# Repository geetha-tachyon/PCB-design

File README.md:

View this project on [CADLAB.io](https://cadlab.io/project/30245). 

# PCB-design
pcb design of stm32 and pressure sensor

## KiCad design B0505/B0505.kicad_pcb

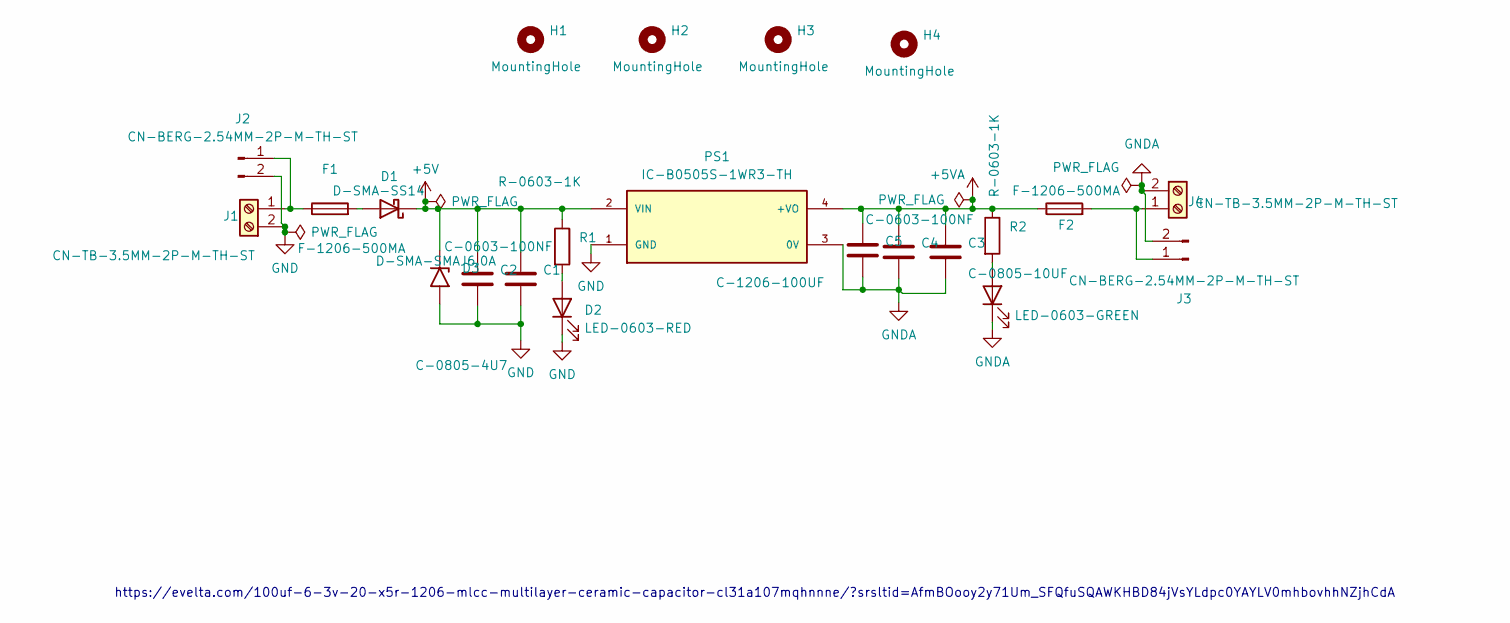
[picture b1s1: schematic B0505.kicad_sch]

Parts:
C1: C-0805-4U7; C_0805_2012Metric
C2, C4: C-0603-100NF; C_0603_1608Metric
C3: C-0805-10UF; C_0805_2012Metric
C5: C-1206-100UF; C_1206_3216Metric
D1: D-SMA-SS14; D_SMA
D2: LED-0603-RED; LED_0603_1608Metric
D3: D-SMA-SMAJ6.0A; D_SMA
D6: LED-0603-GREEN; LED_0603_1608Metric
F1, F2: F-1206-500MA; Fuse_1206_3216Metric
H1, H2, H3, H4: MountingHole; MountingHole_3.2mm_M3
J1, J4: CN-TB-3.5MM-2P-M-TH-ST; TerminalBlock_Phoenix_PT-1,5-2-3.5-H_1x02_P3.50mm_Horizontal
J2, J3: CN-BERG-2.54MM-2P-M-TH-ST; PinHeader_1x02_P2.54mm_Vertical
PS1: IC-B0505S-1WR3-TH; CONV_B0505S-1WR3-TH; PARTREV 2018.06.29-A/2
R1, R2: R-0603-1K; R_0603_1608Metric

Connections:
+5V: C1.1, C2.1, D1.1 (K), D3.1 (A1), PS1.2 (VIN), R1.1
+5VA: C3.1, C4.1, C5.1, F2.1, PS1.4 (+VO), R2.1
GND: C1.2, C2.2, D2.1 (K), D3.2 (A2), J1.2, J2.2, PS1.1 (GND)
GNDA: C3.2, C4.2, C5.2, D6.1 (K), J3.2, J4.2, PS1.3 (0V)
unnamed: D1.2 (A), F1.2
unnamed: D2.2 (A), R1.2
unnamed: D6.2 (A), R2.2
unnamed: F1.1, J1.1, J2.1
unnamed: F2.2, J3.1, J4.1

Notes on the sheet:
https://evelta.com/100uf-6-3v-20-x5r-1206-mlcc-multilayer-ceramic-capacitor-cl31a107mqhnnne/?srsltid=AfmBOooy2y71Um_SFQfuSQAWKHBD84jVsYLdpc0YAYLV0mhbovhhNZjhCdA

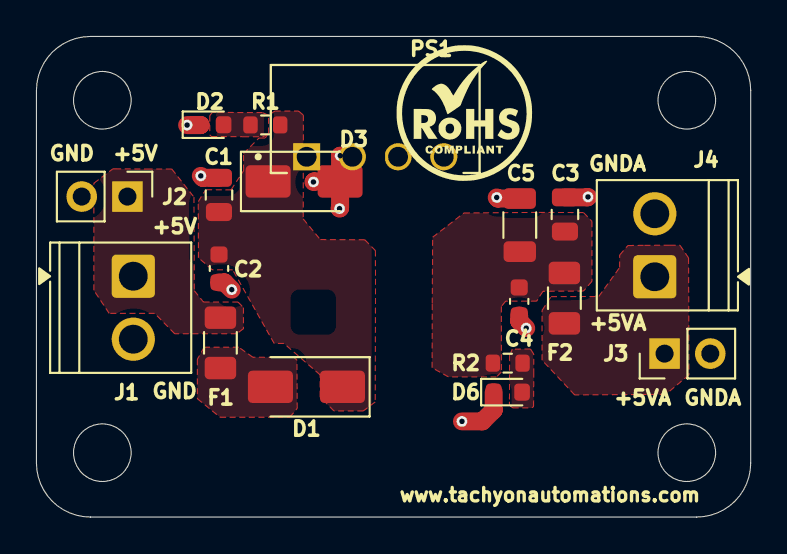
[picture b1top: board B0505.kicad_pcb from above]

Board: 2 copper layers, 39.7 x 26.7 mm, 22 parts (0 on the bottom side), 9 nets.

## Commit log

2026-04-03 Backlink to CADLAB.io has been added.
2026-04-03 B0505
    Sample projevt for cadlab.io
2026-04-03 changes made
    to check the cadlab.io
2026-04-03 moved holes and changed gnd near d6
2026-04-03 moved ps1
